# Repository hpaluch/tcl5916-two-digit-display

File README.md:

# Connecting 7-segment 2-digit display to TLC5916

Here is project how to use 2x TLC5916 with 7-segment 2-digit
LED display.

Board revision 1.0 (initial) is shown on picture.

Project status:

Board was tested successfully. See 
subproject [Connecting TLC5916 to PC using LC 341A USB adapter][Connecting TLC5916 to PC using LC 341A USB adapter] for example.

# Design files

Design files are in revision 1.1, 2019-03-10. New values
of R1 and R2 were computed using this setup:

The relation between R<sub>ext</sub> and I<sub>led</sub> is following
(default configuration after power-up):

1. To get `I_led` in `[mA]` from `R_ext` in `[kOhm]` use:

   ```
   I_led = 1.25 * 15 / R_ext = 18.75 / R_ext
   ```
   
   For example (used in our circuit now): `R_ext = 1 [kOhm]` => `I_led = 18.75 [mA]` 
   
2. To get `R_ext` in `[kOhm]` from `I_led` in `[mA]` use:

   ```
   R_ext = 1.25 * 15 / I_led = 18.75 / I_led
   ```    

   For example: `I_led = 20 [mA]` => `R_ext = 0.937 [kOhm] = 937 [Ohm]`

Also see `Figure 4. Output Current vs Output Voltage` in data sheet
to verify that `VLED` (voltage connected to common LED anode) 
must be greater than `Voltage drop on LED` + `1V` (roughly).
In our case using `+5V` voltage is OK.

Design was done in [Eagle 9.3.0 Free][Eagle 9.3.0 Free]

Schematic is:

Also in:
* [PDF version][Schematic PDF]
* [Eagle 9.3.0 Free version][Schematic Eagle]

PCB design is:

Also in:
* [PDF version][PCB PDF]
* [Eagle 9.3.0 Free version][PCB Eagle]

Following Eagle libraries were used:

* [zlalanne/eagle-library][zlalanne/eagle-library] for
  definition of [TLC5916][TLC5916]
* [moje.lbr][moje.lbr] - my own part library (originally for Eagle 3/DOS)
  made in late 90's in college - 
  used definition of [2-digit HD-A544D LED display][HD-A544D]

Board was made by [gatema.cz][gatema.cz] for
around 700 CZK (roughly 32 USD) including:

* 2 layers
* plated holes
* solder mask
* top silk screen

NOTE: Remember to follow instructions in 
[eagle-dokumentace.pdf][eagle-dokumentace.pdf]
from [Technicke informace][Technicke informace]
(provided in Czech only)

# Bill of Material

* 2x [TLC5916][TLC5916 - tme.eu] - from tme.eu
* LED display [HD-A544D][HD-A544D] - from gme.cz
* 2x 1K resistor - from my inventory
* 2x 100nF capacitor - from my inventory
* pinhead connector 6 pins in 1 row - used
  20-pin [DS1021-1x20SF1-10][DS1021-1x20SF1-10] - from gme.cz

# Connecting TLC5916 to Interfaces

There are following subprojects:
* [Connecting TLC5916 to PC using LC 341A USB adapter][Connecting TLC5916 to PC using LC 341A USB adapter] - connecting
  this board to PC with USB adapter

# Known bugs/limitations

Design shortcomings:
* digital signals (`CLK`, `SDI`, `SDO`, `LE`) should be routed more
  carefully - not crossing `LED` lines (where are high current spikes).
* LED display power supply pins (`13` and `14`) should be
  wired  to `+5V` supply through jumper pins
  to allow custom power supply (for example `+12V`) different
  from main circuit `+5V` power supply.

[Technicke informace]: https://www.gatema.cz/plosne-spoje/technicke-informace/default/7?do=reloadInfo
[eagle-dokumentace.pdf]: http://www.gatema.cz/file-link/eagle-dokumentace.pdf
[gatema.cz]: https://extranet.gatema.cz/dps/konfiguratorpool.aspx
[DS1021-1x20SF1-10]: https://www.gme.cz/oboustranny-kolik-s1g20-2-54mm-v-13-80mm
[TLC5916 - tme.eu]: https://www.tme.eu/en/details/tlc5916in/led-drivers/texas-instruments/
[Connecting TLC5916 to PC using LC 341A USB adapter]: https://github.com/hpaluch/tlc5916-two-digit-display/tree/master/ch341-tlc5916
[HD-A544D]: https://www.gme.cz/led-display-14-2mm-red-hd-a544d
[moje.lbr]: https://github.com/hpaluch/tlc5916-two-digit-display/blob/master/Eagle/moje.lbr?raw=true
[TLC5916]: http://www.ti.com/lit/ds/slvs695d/slvs695d.pdf
[zlalanne/eagle-library]: https://github.com/zlalanne/eagle-library/blob/master/lbr/zlalanne.lbr
[PCB Eagle]: https://github.com/hpaluch/tlc5916-two-digit-display/blob/master/Eagle/tlc5916-2seg.brd?raw=true
[PCB PDF]: https://github.com/hpaluch/tlc5916-two-digit-display/blob/master/Eagle/tlc5916-2seg-pcb.pdf?raw=true
[Schematic Eagle]: https://github.com/hpaluch/tlc5916-two-digit-display/blob/master/Eagle/tlc5916-2seg.sch?raw=true
[Schematic PDF]: https://github.com/hpaluch/tlc5916-two-digit-display/blob/master/Eagle/tlc5916-2seg-sch.pdf?raw=true
[Eagle 9.3.0 Free]: https://www.autodesk.com/products/eagle/free-download

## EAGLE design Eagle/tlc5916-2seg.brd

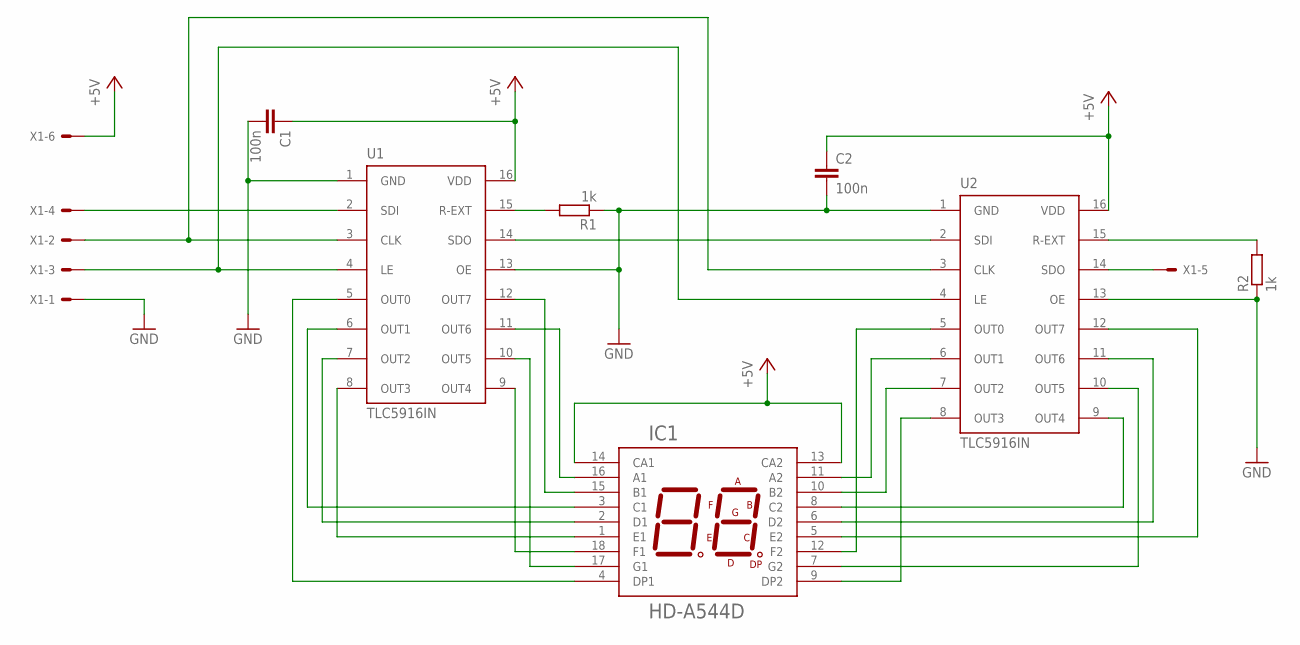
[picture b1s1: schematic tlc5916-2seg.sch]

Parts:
C1, C2: 100n; C5B3
IC1: HD-A544D; DIL18-SE
R1, R2: 1k; 0207/10
U1, U2: TLC5916IN; DIL16
X1: 22-23-2061

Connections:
+5V: C1.1, C2.1, IC1.13 (CA2), IC1.14 (CA1), U1.16 (VDD), U2.16 (VDD), X1.6
GND: C1.2, C2.2, R1.1, R2.1, U1.1 (GND), U1.13 (OE), U2.1 (GND), U2.13 (OE), X1.1
unnamed: R1.2, U1.15 (R-EXT)
unnamed: U1.3 (CLK), U2.3 (CLK), X1.2
unnamed: U1.4 (LE), U2.4 (LE), X1.3
unnamed: U1.2 (SDI), X1.4
unnamed: U1.14 (SDO), U2.2 (SDI)
unnamed: U2.14 (SDO), X1.5
unnamed: IC1.15 (B1), U1.12 (OUT7)
unnamed: R2.2, U2.15 (R-EXT)
unnamed: IC1.16 (A1), U1.11 (OUT6)
unnamed: IC1.17 (G1), U1.10 (OUT5)
unnamed: IC1.18 (F1), U1.9 (OUT4)
unnamed: IC1.1 (E1), U1.8 (OUT3)
unnamed: IC1.2 (D1), U1.7 (OUT2)
unnamed: IC1.3 (C1), U1.6 (OUT1)
unnamed: IC1.4 (DP1), U1.5 (OUT0)
unnamed: IC1.12 (F2), U2.5 (OUT0)
unnamed: IC1.11 (A2), U2.6 (OUT1)
unnamed: IC1.10 (B2), U2.7 (OUT2)
unnamed: IC1.9 (DP2), U2.8 (OUT3)
unnamed: IC1.8 (C2), U2.9 (OUT4)
unnamed: IC1.7 (G2), U2.10 (OUT5)
unnamed: IC1.6 (D2), U2.11 (OUT6)
unnamed: IC1.5 (E2), U2.12 (OUT7)

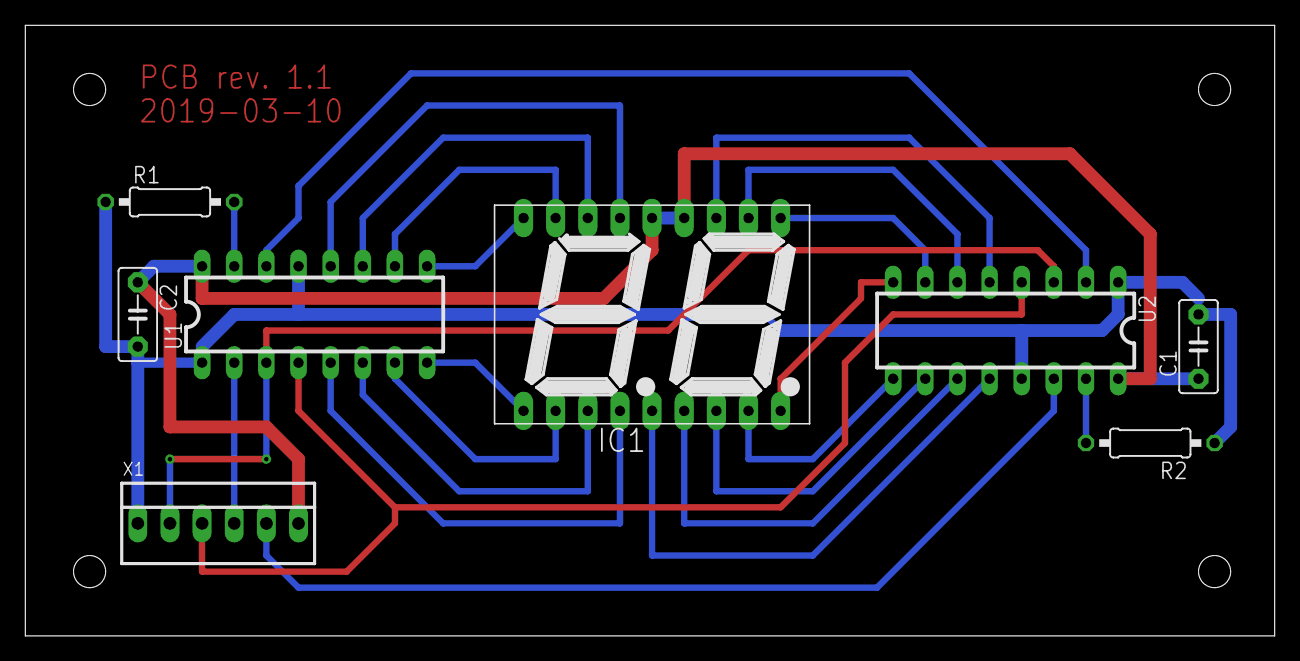
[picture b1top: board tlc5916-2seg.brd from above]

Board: 2 copper layers, 98.7 x 48.2 mm, 8 parts (0 on the bottom side), 25 nets.

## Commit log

2019-03-03 Design files
2019-03-03 Reference (most) design files
2019-03-03 Added links to used libraries
2019-03-03 Fixed Eagle version
2019-03-03 Lower values for R1 and R2
2019-03-03 Known design limitations
2019-03-03 better wording
2019-03-03 Using LC CH341A to access TL5916
2019-03-03 Use 'Fake /SS' signal for SPI decoder in Logic Analyzer
2019-03-03 Interlinking CH341 subproject and Analyzer output
2019-03-03 Fixed links and table
2019-03-03 Attempt to workaround footnote
2019-03-03 Fixed ugly typo PCI/PC
2019-03-03 Completed decoder for 1st digit
2019-03-03 Fixed links mismatch
2019-03-03 Added BOM
2019-03-04 Typo TLC -> TCL
2019-03-04 Fixed project urls tcl -> tlc
2019-03-04 Finally got rid of tcl typo
2019-03-04 Use common name for USB adapter
2019-03-04 Equation for I_led and R_ext
2019-03-09 Support for 2 digits - tested on PCB
2019-03-09 Added photo of finished PCB
2019-03-09 Fixed link
2019-03-10 Updted R1, R2 to 1K (from 5K), added schematics Frame
2019-03-10 Fixed R1, R2 values, added revision number to PCB
2019-03-10 Again TCL/TLC
